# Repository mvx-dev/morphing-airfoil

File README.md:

# DESN1K Morphing Wing Main Repository
---
The main repository for uploading project files for the morphing wing project.

## Directories
---
Airfoils: any files relating to airfoil design. This include txt files, STL files, and Solidworks part files

Minutes: the minutes for every meeting

Embedded Systems: all files relating to embedded system design. This includes schematics, PCB files, etc

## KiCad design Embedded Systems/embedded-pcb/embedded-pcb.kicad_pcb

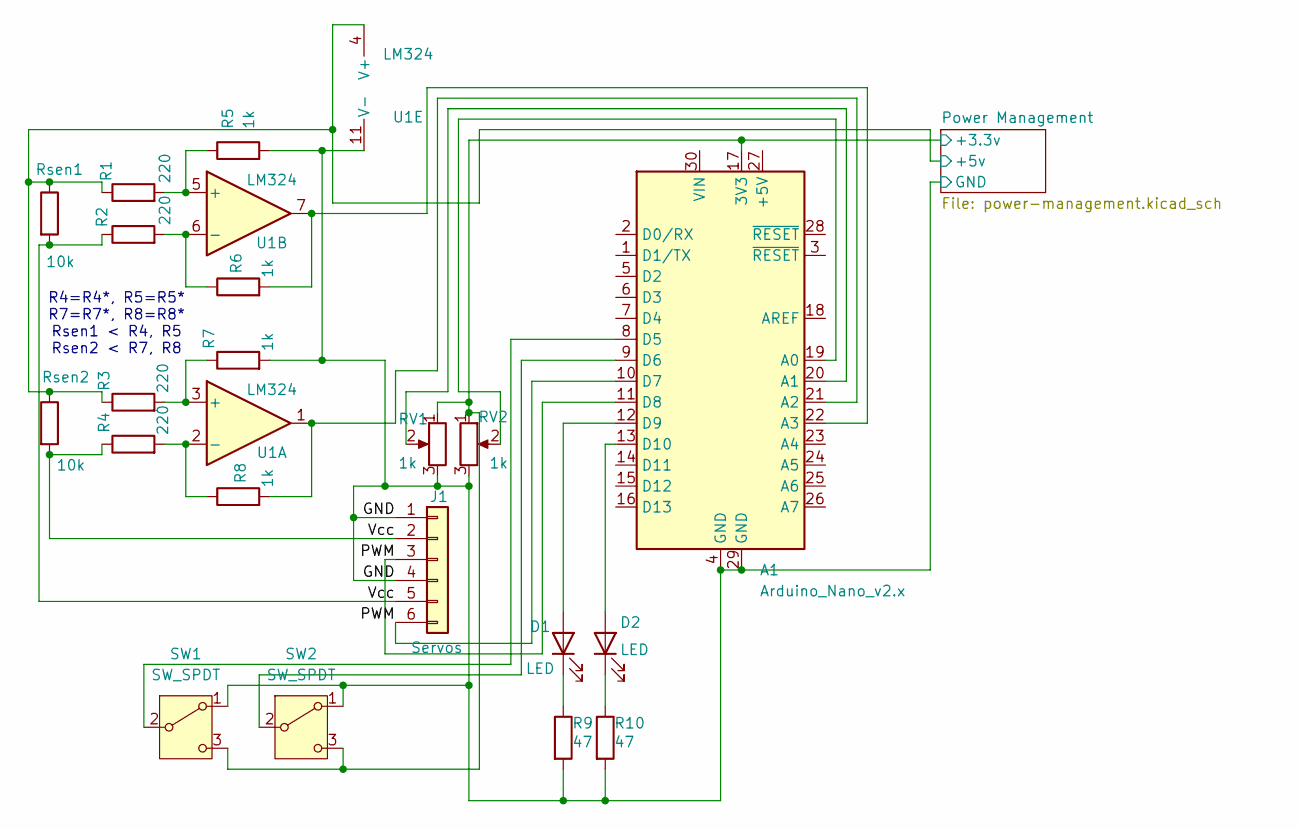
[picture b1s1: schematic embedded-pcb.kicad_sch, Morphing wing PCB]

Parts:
A1: Arduino_Nano_v2.x; Arduino_Nano
D1, D2: LED; LED_D5.0mm
J1: Servos; PinSocket_1x06_P2.54mm_Vertical
R1, R2, R3, R4: 220; R_Axial_DIN0207_L6.3mm_D2.5mm_P10.16mm_Horizontal
R5, R6, R7, R8: 1k; R_Axial_DIN0207_L6.3mm_D2.5mm_P10.16mm_Horizontal
R9, R10: 47; R_Axial_DIN0207_L6.3mm_D2.5mm_P10.16mm_Horizontal
RV1, RV2: 1k; SolderWire-0.1sqmm_1x03_P3.6mm_D0.4mm_OD1mm
Rsen1, Rsen2: 10k; R_Axial_DIN0207_L6.3mm_D2.5mm_P10.16mm_Horizontal
SW1, SW2: SW_SPDT; SolderWire-0.1sqmm_1x03_P3.6mm_D0.4mm_OD1mm
U1: LM324; DIP-14_W7.62mm

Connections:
/GND: A1.4 (GND), A1.29 (GND), J1.1, J1.4, R5.2, R7.2, R9.2, R10.2, RV1.3, RV2.3, SW1.1 (A), SW2.1 (A), U1.11 (V-); also elsewhere on the board
/PWM: A1.10 (D7), A1.11 (D8), J1.3, J1.6
/Power Management/+3.3v: A1.17 (3V3), RV1.1, RV2.1, SW1.3 (C), SW2.3 (C); also elsewhere on the board
/Power Management/+5v: R1.1, R3.1, Rsen1.1, Rsen2.1, U1.4 (V+); also elsewhere on the board
/Vcc: J1.2, J1.5, R2.1, R4.1, Rsen1.2, Rsen2.2
unnamed: A1.19 (A0), RV2.2
unnamed: A1.20 (A1), RV1.2
unnamed: A1.21 (A2), R8.2, U1.1
unnamed: A1.22 (A3), R6.2, U1.7
unnamed: A1.8 (D5), SW1.2 (B)
unnamed: A1.9 (D6), SW2.2 (B)
unnamed: A1.12 (D9), D1.2 (A)
unnamed: A1.13 (D10), D2.2 (A)
unnamed: D1.1 (K), R9.1
unnamed: D2.1 (K), R10.1
unnamed: R3.2, R7.1, U1.3 (+)
unnamed: R4.2, R8.1, U1.2 (-)
unnamed: R1.2, R5.1, U1.5 (+)
unnamed: R2.2, R6.1, U1.6 (-)

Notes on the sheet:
R4=R4*, R5=R5* R7=R7*, R8=R8* Rsen1 < R4, R5 Rsen2 < R7, R8

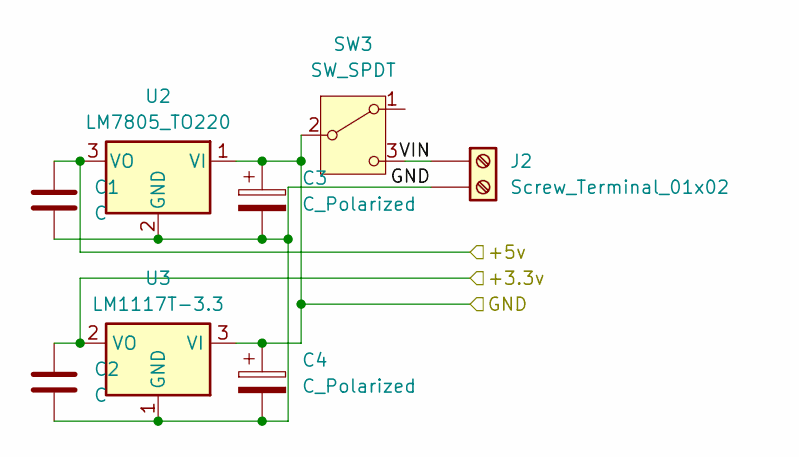
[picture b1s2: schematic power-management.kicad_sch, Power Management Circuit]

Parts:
C1, C2: C; C_Disc_D3.8mm_W2.6mm_P2.50mm
C3, C4: C_Polarized; CP_Radial_D5.0mm_P2.50mm
J2: Screw_Terminal_01x02; TerminalBlock_bornier-2_P5.08mm
SW3: SW_SPDT; SolderWire-0.1sqmm_1x03_P3.6mm_D0.4mm_OD1mm
U2: LM7805_TO220; TO-220-3_Vertical
U3: LM1117T-3.3; TO-220-3_Vertical

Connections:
/GND: C1.2, C2.2, C3.1, C3.2, C4.1, C4.2, J2.2, SW3.2 (B), U2.1 (VI), U2.2 (GND), U3.1 (GND), U3.3 (VI); also elsewhere on the board
/Power Management/+3.3v: C2.1, U3.2 (VO); also elsewhere on the board
/Power Management/+5v: C1.1, U2.3 (VO); also elsewhere on the board
/Power Management/VIN: J2.1, SW3.3 (C)

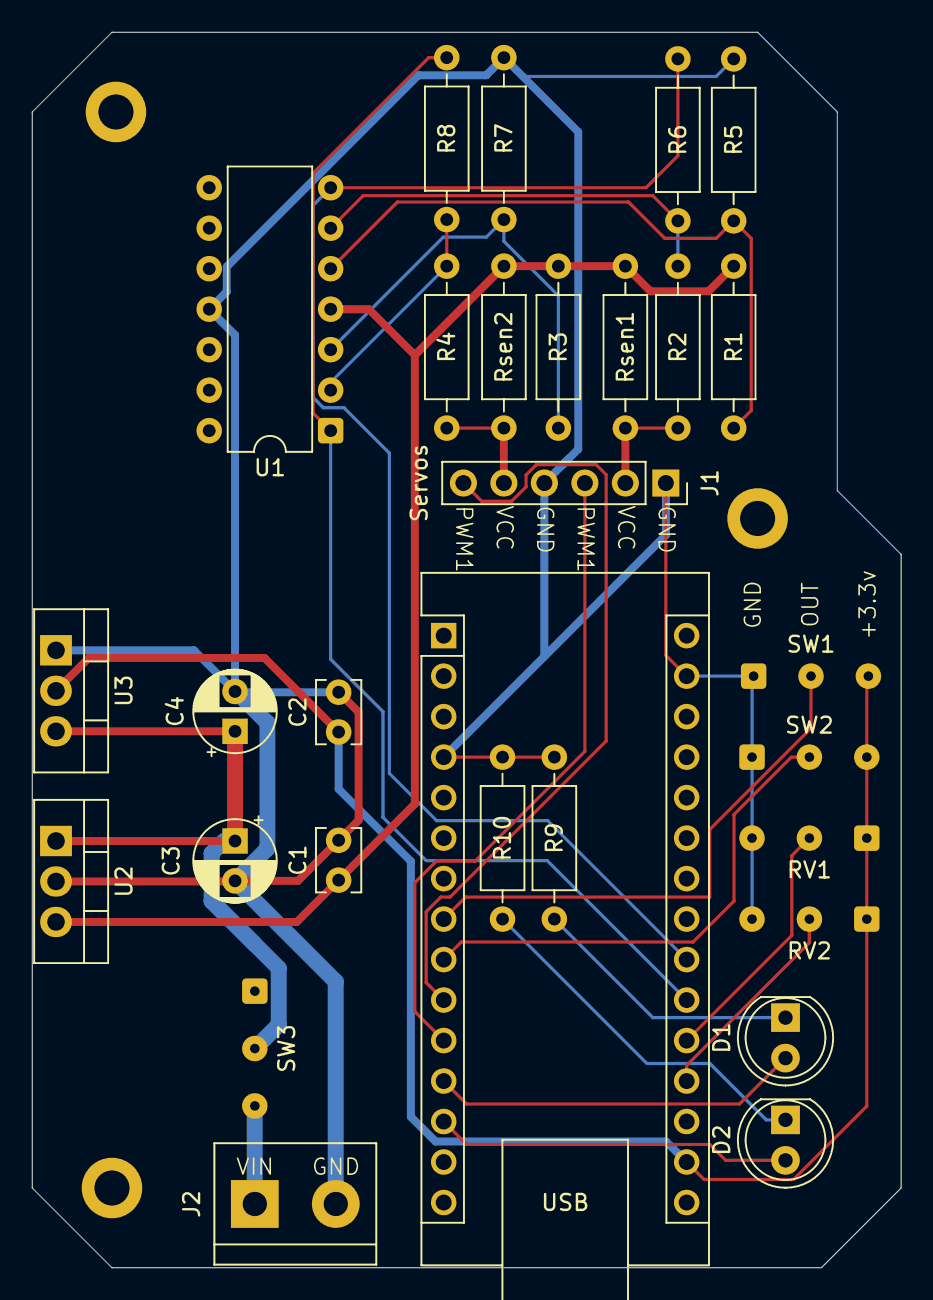
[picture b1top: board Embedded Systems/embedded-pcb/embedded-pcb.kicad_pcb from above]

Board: 2 copper layers, 54.5 x 77.5 mm, 29 parts (0 on the bottom side), 20 nets.

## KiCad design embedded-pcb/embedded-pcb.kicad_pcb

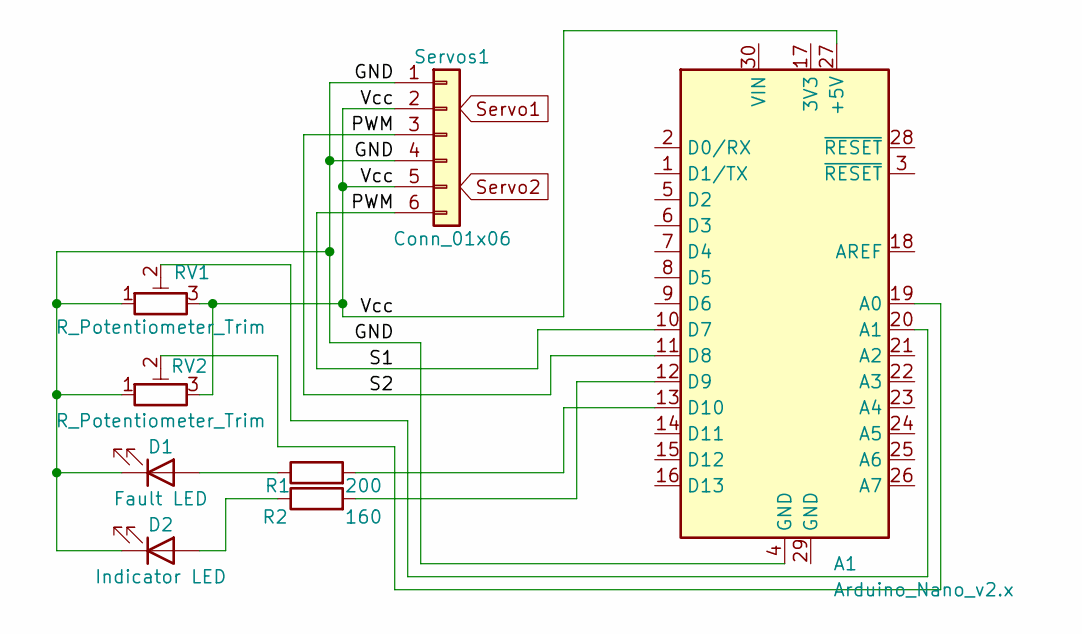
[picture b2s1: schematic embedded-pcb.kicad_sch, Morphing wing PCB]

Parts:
A1: Arduino_Nano_v2.x; Arduino_Nano
D1: Fault LED; LED_D5.0mm_Horizontal_O1.27mm_Z9.0mm
D2: Indicator LED; LED_D5.0mm_Horizontal_O1.27mm_Z9.0mm
R1: 200; R_Axial_DIN0207_L6.3mm_D2.5mm_P10.16mm_Horizontal
R2: 160; R_Axial_DIN0207_L6.3mm_D2.5mm_P10.16mm_Horizontal
RV1, RV2: R_Potentiometer_Trim; Potentiometer_ACP_CA9-H2,5_Horizontal
Servos1: Conn_01x06; PinSocket_1x06_P2.54mm_Vertical

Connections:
/GND: A1.4 (GND), D1.1 (K), D2.1 (K), RV1.1, RV2.1, Servos1.1, Servos1.4
/PWM: A1.10 (D7), A1.11 (D8), Servos1.3, Servos1.6
/Vcc: A1.27 (+5V), RV1.3, RV2.3, Servos1.2, Servos1.5
unnamed: A1.19 (A0), RV2.2
unnamed: A1.20 (A1), RV1.2
unnamed: A1.12 (D9), R2.2
unnamed: A1.13 (D10), R1.2
unnamed: D1.2 (A), R1.1
unnamed: D2.2 (A), R2.1

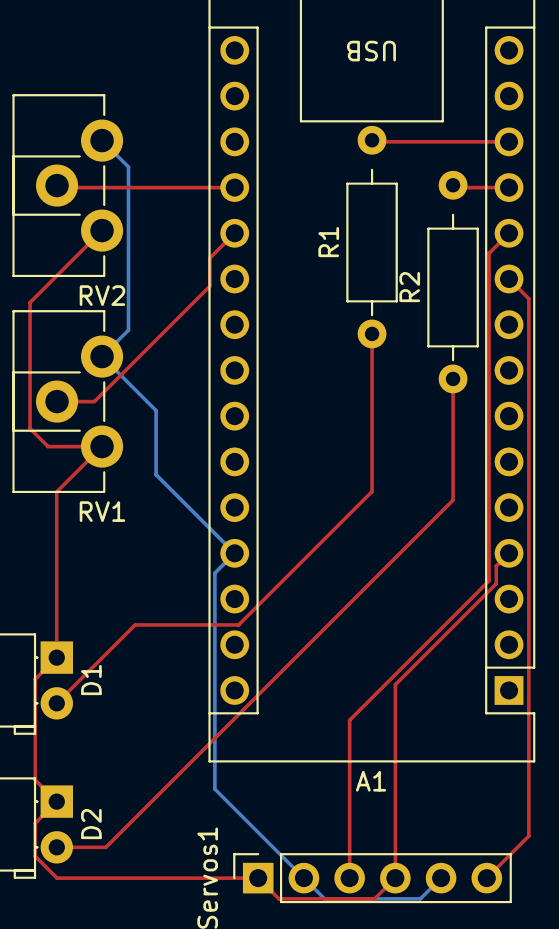
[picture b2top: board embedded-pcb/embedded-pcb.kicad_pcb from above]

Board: 2 copper layers, 8 parts (0 on the bottom side), 9 nets.

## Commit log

2025-02-24 feat: initial commit
2025-02-27 feat: Update README.md
2025-02-28 Added meeting minutes
2025-03-10 feat: SG90 solidworks part
    3D model of the SG90 servo motor for use in the morphing wing
2025-03-10 feat: Added meeting minutes
    Added meeting minutes for 10/03/2025 7:45pm
2025-03-14 feat: embedded system project files
2025-03-15 feat: added schematic for embedded systems
    Designed a basic PCB for the embedded system
2025-03-15 remove: temporary program file
2025-03-17 feat: small update to schematic
2025-03-17 feat: single servo control
    Code for controlling a single servo using a trim pot
2025-03-18 feat: optimised tracks
2025-03-19 update: latest backup for schematic
2025-03-19 feat: airfoil models
    Created 3D models for NACA 2412, NACA 2414, NACA 4414
2025-03-19 refactor: embedded-systems
    Rearranged the file structure of the embedded systems files
2025-03-19 feat: uploaded minutes
2025-03-20 feat: uploaded compliant mechanism
    Added DXF file for the first revision for a compliant mechanism.
2025-03-20 refactor: rearranged mechanism files
2025-03-20 feat: Airfoil compliant mechanism revision 2
2025-03-22 feat: updated schematic
2025-03-24 feat: uploaded first flexible skin design
2025-03-25 feat: updated schematic for 3.3v
2025-03-25 feat: uploaded flexible skin designs
2025-03-27 feat: updated schematic PDF
2025-04-03 feat: added smoothing
    Added the ability to smooth the output of the potentiometers for servo control.
2025-04-03 feat: fixed smoothing
2025-04-03 feat: cleaned for release version
    Cleaned up the smoothing code, and finished the calibration function. This is v1.0 of the servo control code.
2025-04-07 Add files via upload
    3415, 4615 for wind tunnel testing
    Only the base shapes
2025-04-10 feat: added power management
    Added a basic circuit for power management. Supports 3.3v @ 0.8A and 5v @ 1.5A simultaneously.
2025-04-10 feat: v2 of PCB design
2025-04-11 feat: updated power management
2025-04-11 feat: finalised PCB
    Finalised the electrical design and PCB, including adding a power switch, silksreening, and mounting holes.
2025-04-11 feat: started housing design
2025-04-11 feat: updated ES
    Basic schematic updates, prior versions uploaded
2025-04-16 feat: generated BOM
2025-04-16 feat: first housing iteration
2025-04-17 feat: designed lid
2025-04-25 feat: updated pinout
2025-04-25 feat: updated pcb
2025-04-25 feat: generated parts list
